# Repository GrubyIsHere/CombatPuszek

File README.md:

# CombatPuszek
Fancy combat-type robot with huge saw on top.

## Features
*   ESP32-based remote control system.
*   All-around horizontal saw, up to 250mm in diameter.
*   3lbs (1.36kg) weight category.
*   Two drive configurations: wheels or soft tracks.
*   Swappable motor drivers, main ESC, and even main ESP32 module. 
*   Powered by 3S LiPO.

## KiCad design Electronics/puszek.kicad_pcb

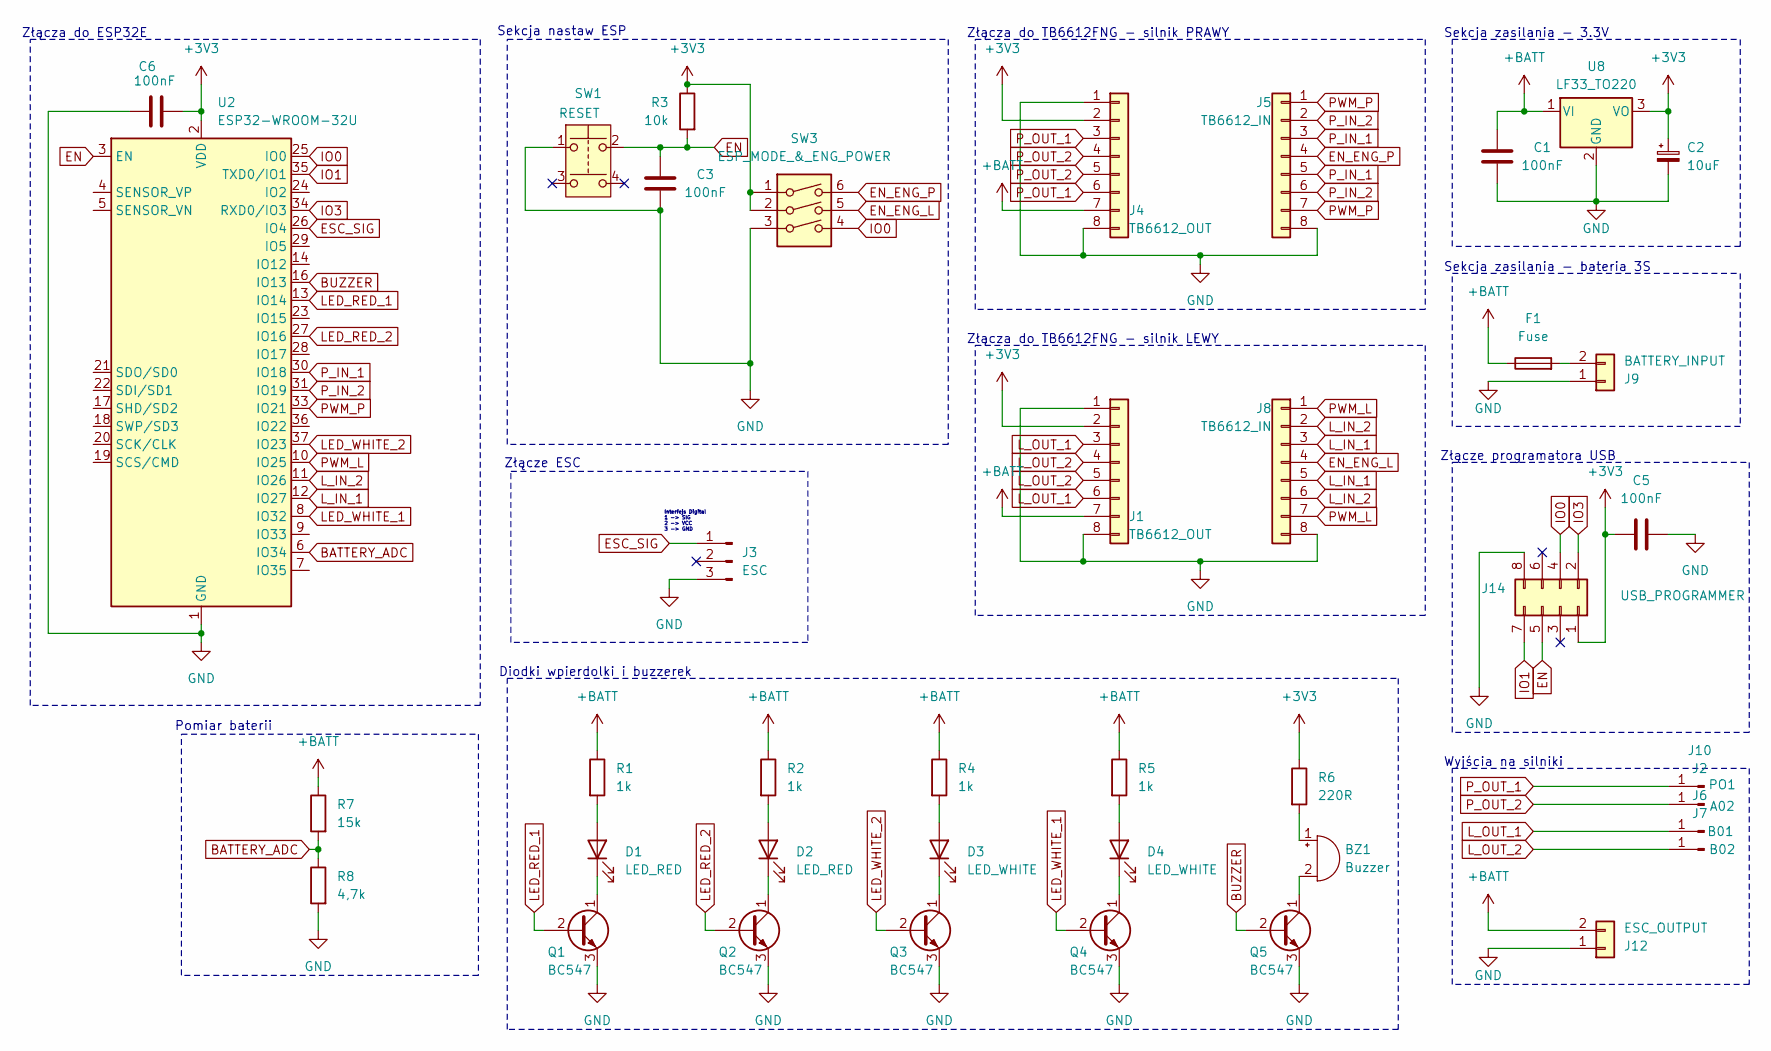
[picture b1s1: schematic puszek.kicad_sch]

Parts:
BZ1: Buzzer; Buzzer_12x9.5RM7.6
C1, C3, C5, C6: 100nF; C_0603_1608Metric
C2: 10uF; CP_Radial_D5.0mm_P2.50mm
D1, D2: LED_RED; LED_D5.0mm
D3, D4: LED_WHITE; LED_D5.0mm
F1: Fuse; Fuse_Littelfuse_395Series
J1, J4: TB6612_OUT; PinHeader_1x08_P2.54mm_Vertical
J2: A02; PinHeader_1x01_P2.54mm_Vertical
J3: ESC; PinHeader_1x03_P2.54mm_Vertical
J5, J8: TB6612_IN; PinHeader_1x08_P2.54mm_Vertical
J6: B01; PinHeader_1x01_P2.54mm_Vertical
J7: B02; PinHeader_1x01_P2.54mm_Vertical
J9: BATTERY_INPUT; AMASS_XT60-F_1x02_P7.20mm_Vertical
J10: PO1; PinHeader_1x01_P2.54mm_Vertical
J12: ESC_OUTPUT; AMASS_XT60-F_1x02_P7.20mm_Vertical
J14: USB_PROGRAMMER; PinHeader_2x04_P2.54mm_Vertical
Q1, Q2, Q3, Q4, Q5: BC547; TO-92_Inline
R1, R2, R4, R5: 1k; R_0603_1608Metric
R3: 10k; R_0603_1608Metric
R6: 220R; R_0603_1608Metric
R7: 15k; R_0603_1608Metric
R8: 4,7k; R_0603_1608Metric
SW1: RESET; SW_PUSH_6mm_H5mm
SW3: ESP_MODE_&_ENG_POWER; SW_DIP_SPSTx03_Slide_9.78x9.8mm_W7.62mm_P2.54mm
U2: ESP32-WROOM-32U; adapter_ESP32_NEW
U8: LF33_TO220; TO-220-3_Horizontal_TabDown

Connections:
+3V3: C2.1, C5.1, C6.1, J1.2, J4.2, J14.1, R3.1, R6.1, SW3.1, SW3.2, U2.2 (VDD), U8.3 (VO)
+BATT: C1.2, F1.1, J1.7, J4.7, J12.2, R1.1, R2.1, R4.1, R5.1, R7.1, U8.1 (VI)
BATTERY_ADC: R7.2, R8.1, U2.6 (IO34)
BUZZER: Q5.2 (B), U2.16 (IO13)
EN: C3.2, J14.5, R3.2, SW1.2, U2.3 (EN)
EN_ENG_L: J8.4, SW3.5
EN_ENG_P: J5.4, SW3.6
ESC_SIG: J3.1, U2.26 (IO4)
GND: C1.1, C2.2, C3.1, C5.2, C6.2, J1.1, J1.8, J3.3, J4.1, J4.8, J5.8, J8.8, J9.1, J12.1, J14.8, Q1.3 (E), Q2.3 (E), Q3.3 (E), Q4.3 (E), Q5.3 (E), R8.2, SW1.1, SW3.3, U2.1 (GND), U2.15 (GND), U2.38 (GND), U2.39 (GND), U8.2 (GND)
IO0: J14.4, SW3.4, U2.25 (IO0)
IO1: J14.7, U2.35 (TXD0/IO1)
IO3: J14.2, U2.34 (RXD0/IO3)
LED_RED_1: Q1.2 (B), U2.13 (IO14)
LED_RED_2: Q2.2 (B), U2.27 (IO16)
LED_WHITE_1: Q4.2 (B), U2.8 (IO32)
LED_WHITE_2: Q3.2 (B), U2.37 (IO23)
L_IN_1: J8.3, J8.5, U2.12 (IO27)
L_IN_2: J8.2, J8.6, U2.11 (IO26)
L_OUT_1: J1.3, J1.6, J6.1
L_OUT_2: J1.4, J1.5, J7.1
unnamed: BZ1.1 (+), R6.2
unnamed: BZ1.2 (-), Q5.1 (C)
unnamed: D1.2 (A), R1.2
unnamed: D1.1 (K), Q1.1 (C)
unnamed: D2.2 (A), R2.2
unnamed: D2.1 (K), Q2.1 (C)
unnamed: D3.2 (A), R4.2
unnamed: D3.1 (K), Q3.1 (C)
unnamed: D4.2 (A), R5.2
unnamed: D4.1 (K), Q4.1 (C)
unnamed: F1.2, J9.2
PWM_L: J8.1, J8.7, U2.10 (IO25)
PWM_P: J5.1, J5.7, U2.33 (IO21)
P_IN_1: J5.3, J5.5, U2.30 (IO18)
P_IN_2: J5.2, J5.6, U2.31 (IO19)
P_OUT_1: J4.3, J4.6, J10.1
P_OUT_2: J2.1, J4.4, J4.5

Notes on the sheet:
Sekcja zasilania - bateria 3S
Pomiar baterii
Wyjścia na silniki
Interfejs Digital 1 -> SIG 2 -> VCC 3 -> GND
Złącza do TB6612FNG - silnik LEWY
Złącza do ESP32E
Złącze programatora USB
Złącza do TB6612FNG - silnik PRAWY
Sekcja nastaw ESP
Złącze ESC
Sekcja zasilania - 3.3V
Diodki wpierdolki i buzzerek

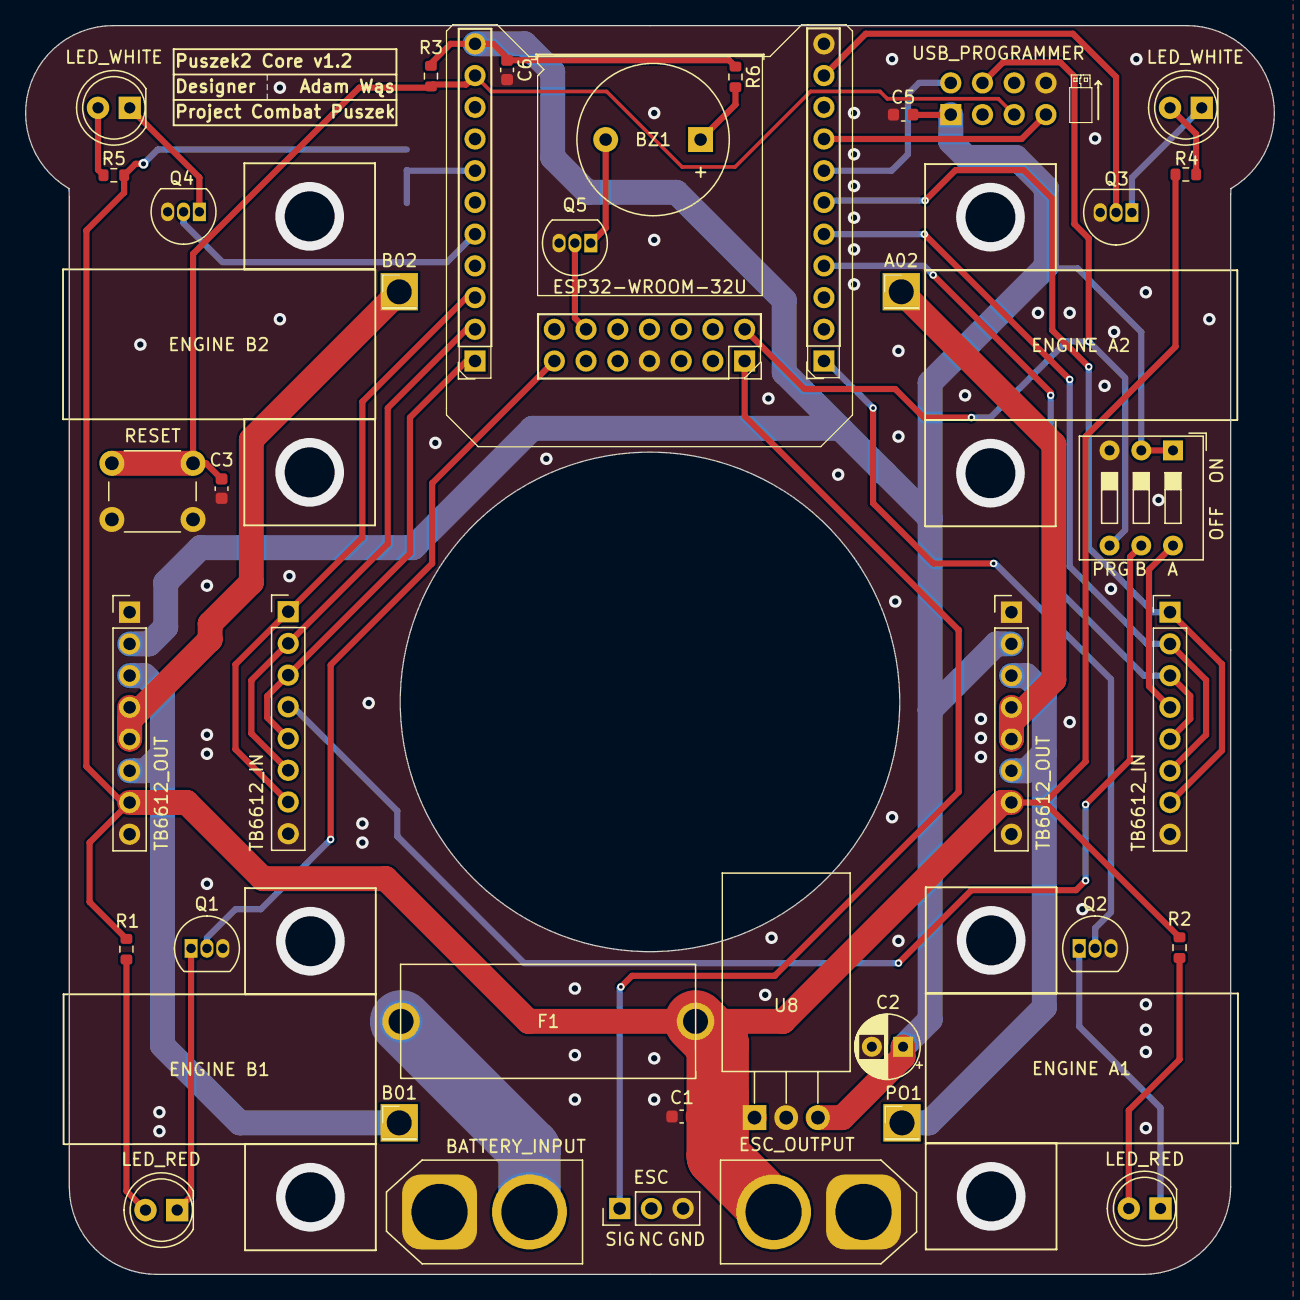
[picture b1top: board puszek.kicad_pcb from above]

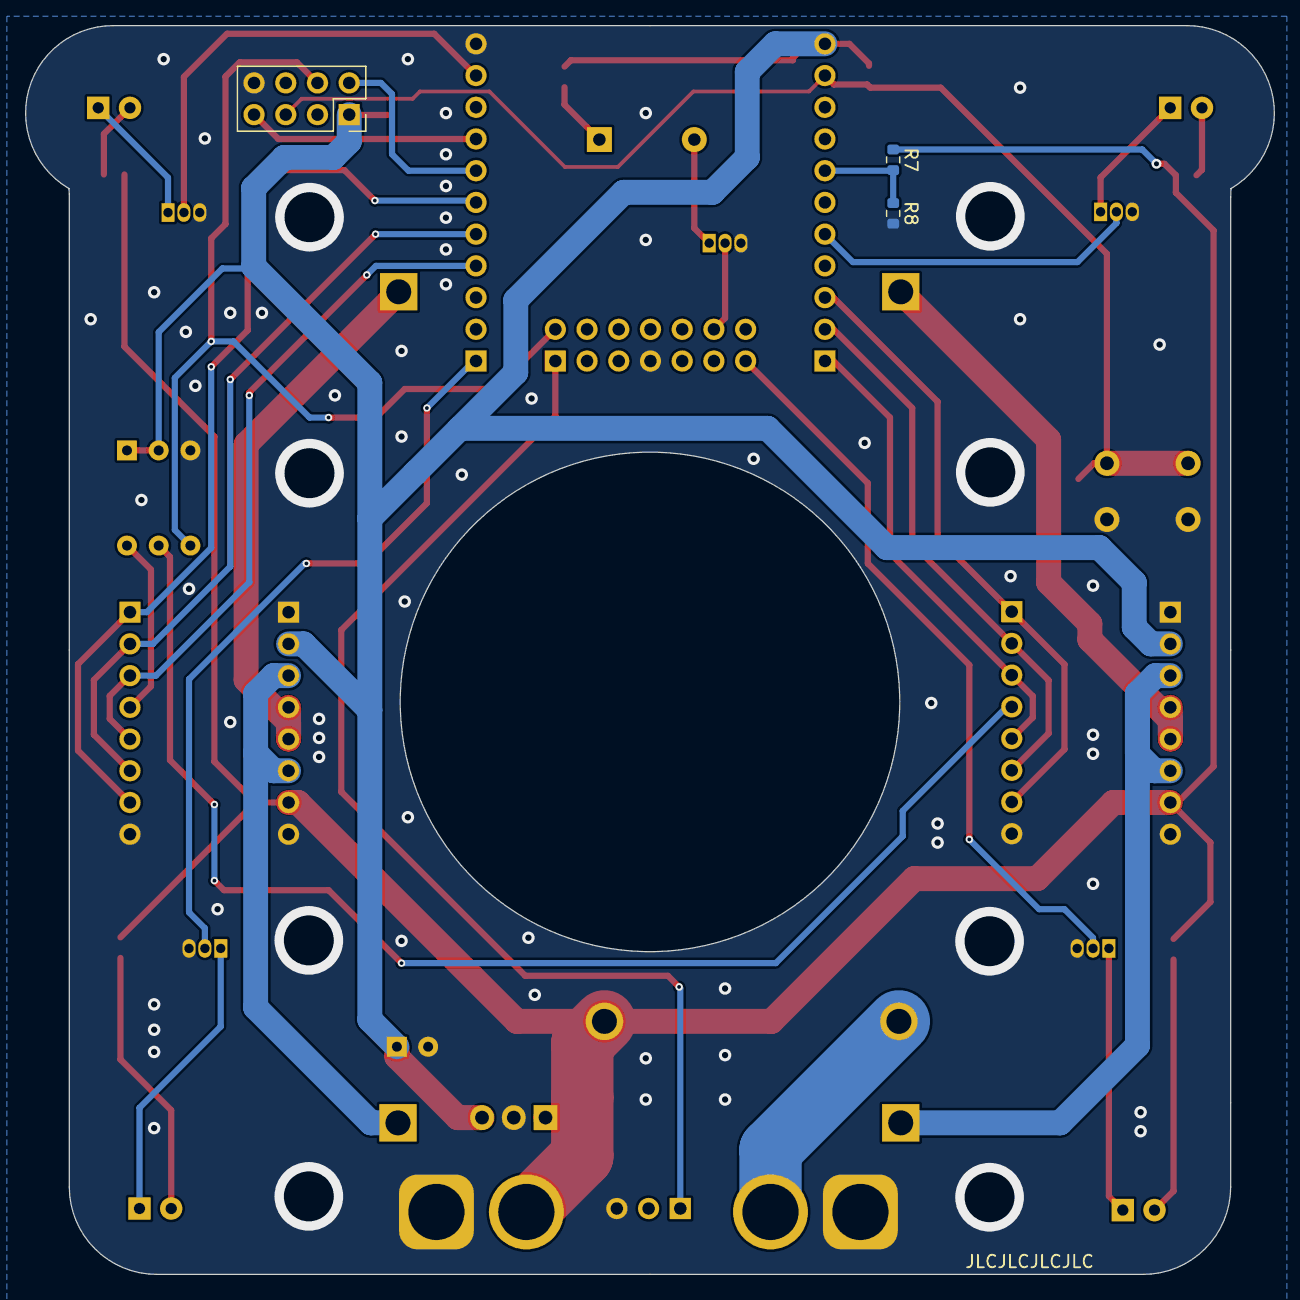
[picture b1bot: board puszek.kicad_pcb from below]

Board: 2 copper layers, 100.0 x 100.0 mm, 40 parts (2 on the bottom side), 37 nets.

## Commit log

2026-01-10 initial full send
2026-01-10 gitignore correction
2026-01-10 anosteh gitignore correction
2026-01-10 last .gitinnore correction
    cache got purged
2026-01-10 another git cache purge
    fixing remaining errors in gitignore xd
2026-03-10 jakiśtam
2026-04-12 minor code and mechanical changes
2026-04-13 communication timings fixes
    kod do wysyłania/odbierania sterowania działa teraz dużo lepiej
2026-04-18 test
2026-04-18 untest
2026-04-19 minor connectivity fixes + new saw bracket model
